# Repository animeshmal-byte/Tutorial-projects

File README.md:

# 🛠️ Tutorial Projects Portfolio

Welcome to my personal engineering repository. This space tracks my continuous development, rapid prototyping sprints, and systems-level learning milestones under **Manifold Labs**.

---

## 🎛️ Project 1: Active N-Channel MOSFET Driver Circuit Module
* **EDA Toolchain:** KiCad 10.0 (Custom Schematic Capture & Layout Routing)
* **Architecture:** N-Channel MOSFET (2N7002) low-side switch configuration acting as an isolated active driver interface.
* **Load Circuitry:** Integrated current-limiting resistor array protecting an active diagnostic LED indicator node and a high-frequency inductive buzzer terminal block.
* **PCB Topology:** 2-layer design featuring a continuous, solid copper pour ground plane (GND) for low-impedance noise isolation and trace safety.
* **Signature Silkscreen:** Custom typographic branding element (`ANIMESH`) embedded directly onto the physical board layer layout.

### 📐 Design Showcase
* **3D Mechanical Render:** Insert your uploaded 3D render image here (e.g., ``)
* **PCB Trace Layout:** Insert your uploaded layout image here (e.g., ``)

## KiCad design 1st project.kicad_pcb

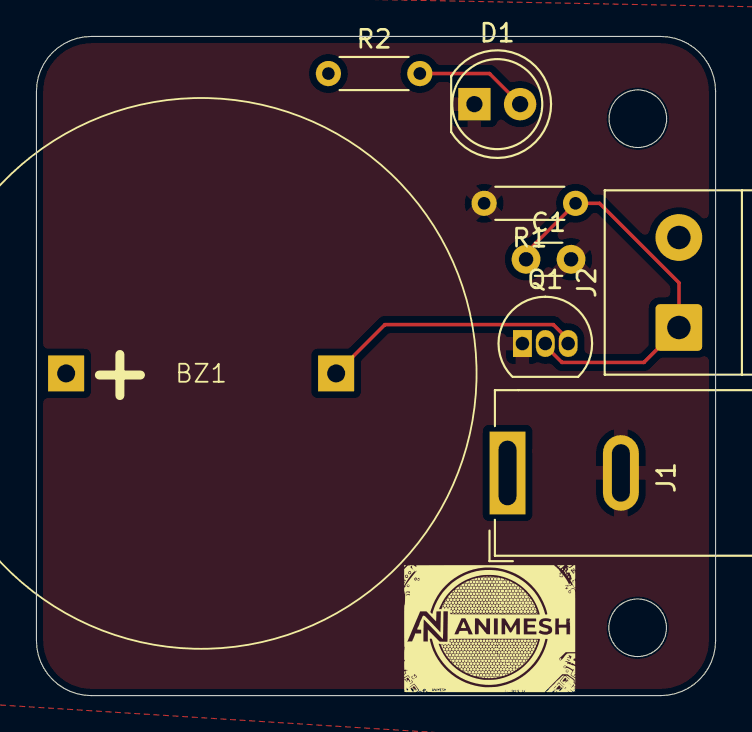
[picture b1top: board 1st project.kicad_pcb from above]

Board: 2 copper layers, 37.7 x 36.6 mm, 8 parts (0 on the bottom side), 5 nets.

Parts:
BZ1: Buzzer; Buzzer_D30mm_H20mm_P15mm__668-1652-ND__AI-3035-TT-12V-R
C1: 1nF; C_Disc_D3.0mm_W1.6mm_P2.50mm
D1: LED_Small_Filled; LED_D5.0mm
J1: Jack-DC; BarrelJack_GCT_DCJ200-10-A_Horizontal
J2: Screw_Terminal_01x02; TerminalBlock_Phoenix_PT-1,5-2-5.0-H_1x02_P5.00mm_Horizontal
Q1: 2N7000; TO-92_Inline
R1: 10M; R_Axial_DIN0204_L3.6mm_D1.6mm_P5.08mm_Horizontal
R2: 6.8k; R_Axial_DIN0204_L3.6mm_D1.6mm_P5.08mm_Horizontal

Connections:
GND: C1.2, D1.1 (K), J1.2, Q1.1 (S), R1.2
unnamed: BZ1.2 (-), Q1.3 (D)
unnamed: D1.2 (A), R2.2
unnamed: C1.1, J2.1, Q1.2 (G), R1.1
VCC: BZ1.1 (+), J1.1, J2.2, R2.1
